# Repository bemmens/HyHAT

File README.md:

To Add: 
- PCB for Array
- PCB for Hypertronics
- Verasonics Code
- BOM
- Link to paper
- Structure of others to add their own designs 

Code to use a Verasonics Vantage System to control the array can be found at: https://github.com/bemmens/Verasonics-Acoustic-Tweezer

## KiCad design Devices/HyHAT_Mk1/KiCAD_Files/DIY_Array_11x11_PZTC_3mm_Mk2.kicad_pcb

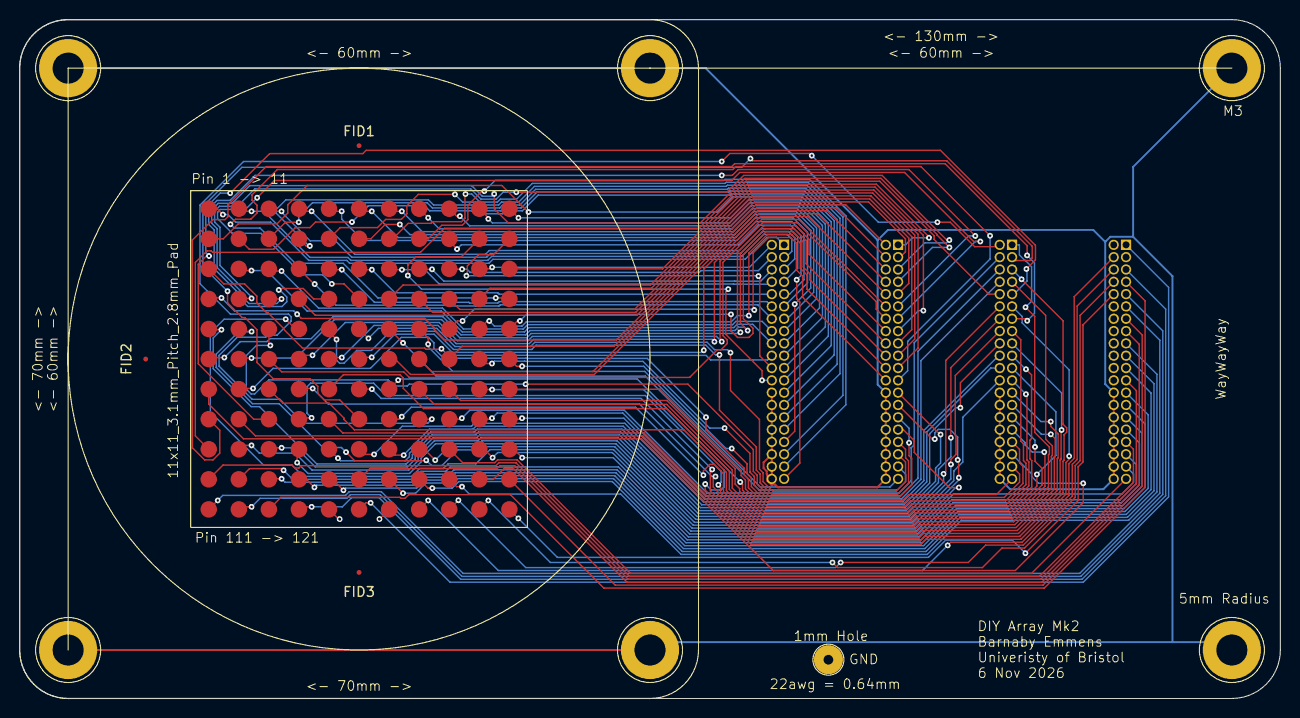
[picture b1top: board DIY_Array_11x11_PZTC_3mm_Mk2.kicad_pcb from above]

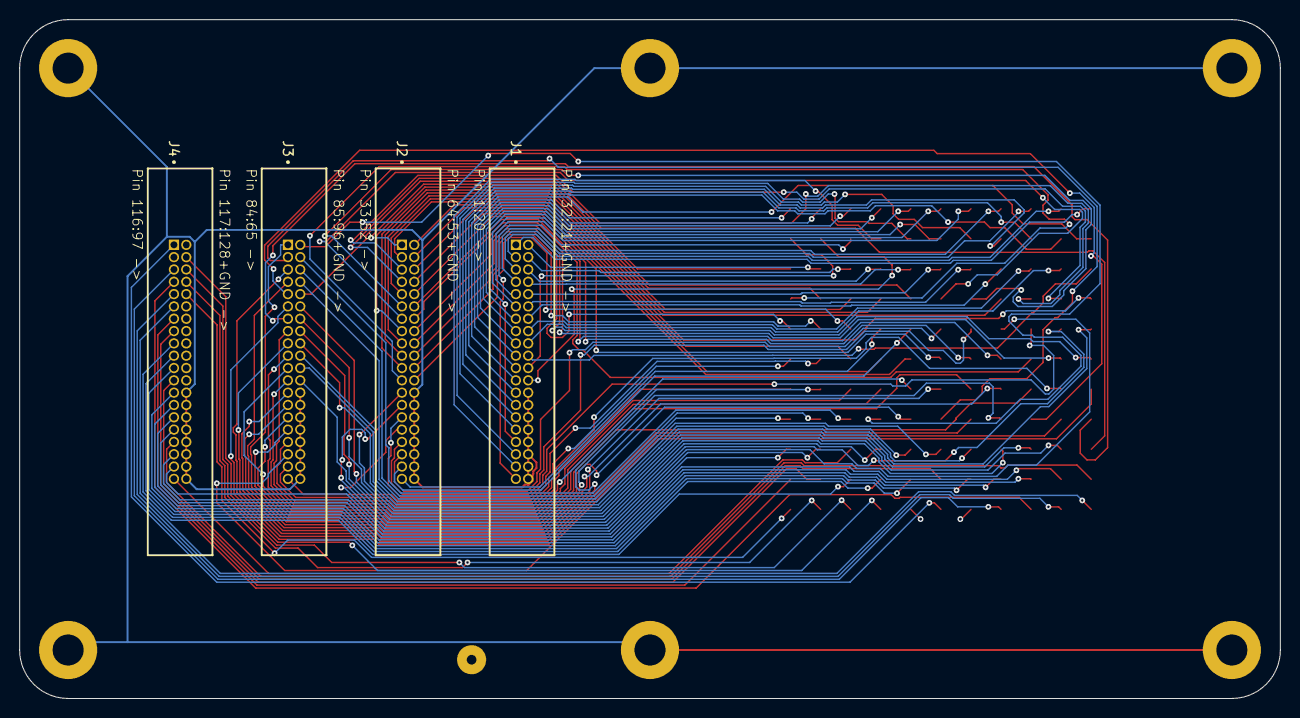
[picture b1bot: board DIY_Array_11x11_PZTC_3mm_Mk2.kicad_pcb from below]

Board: 4 copper layers, 130.0 x 70.0 mm, 15 parts (4 on the bottom side), 122 nets.

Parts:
AR1: PZTC_11x11_3mm_PogoPin
FID1, FID2, FID3: Fiducial_0.5mm_Mask1mm
GND**, GND**1, GND**2, GND**3, GND**4, GND**6: GND_M3
J1, J2, J3, J4: Samtech_2x20; SAMTEC_EHF-120-01-L-D
TP2: TestPoint; PTH_Single_Wire

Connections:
/GND: GND**.1, GND**1.1, GND**2.1, GND**3.1, GND**4.1, GND**6.1, J1.26, J1.28, J1.30, J1.32, J1.34, J1.36, J1.38, J1.40, J2.26, J2.28, J2.30, J2.32, J2.34, J2.36, J2.38, J2.40, J3.26, J3.28, J3.30, J3.32, J3.34, J3.36, J3.38, J3.40, J4.26, J4.28, J4.30, J4.32, J4.34, J4.36, J4.38, J4.40
/L1: AR1.1, J1.1
/L2: AR1.2, J1.3
/L3: AR1.3, J1.5
/L4: AR1.4, J1.7
/L5: AR1.5, J1.9
/L6: AR1.6, J1.11
/L7: AR1.7, J1.13
/L8: AR1.8, J1.15
/L9: AR1.9, J1.17
/L10: AR1.10, J1.19
/L11: AR1.11, J1.21
/L12: AR1.12, J1.23
/L13: AR1.13, J1.25
/L14: AR1.14, J1.27
/L15: AR1.15, J1.29
/L16: AR1.16, J1.31
/L17: AR1.17, J1.33
/L18: AR1.18, J1.35
/L19: AR1.19, J1.37
/L20: AR1.20, J1.39
/L21: AR1.21, J1.2
/L22: AR1.22, J1.4
/L23: AR1.23, J1.6
/L24: AR1.24, J1.8
/L25: AR1.25, J1.10
/L26: AR1.26, J1.12
/L27: AR1.27, J1.14
/L28: AR1.28, J1.16
/L29: AR1.29, J1.18
/L30: AR1.30, J1.20
/L31: AR1.31, J1.22
/L32: AR1.32, J1.24
/L33: AR1.33, J2.1
/L34: AR1.34, J2.3
/L35: AR1.35, J2.5
/L36: AR1.36, J2.7
/L37: AR1.37, J2.9
/L38: AR1.38, J2.11
/L39: AR1.39, J2.13
/L40: AR1.40, J2.15
/L41: AR1.41, J2.17
/L42: AR1.42, J2.19
/L43: AR1.43, J2.21
/L44: AR1.44, J2.23
/L45: AR1.45, J2.25
/L46: AR1.46, J2.27
/L47: AR1.47, J2.29
/L48: AR1.48, J2.31
/L49: AR1.49, J2.33
/L50: AR1.50, J2.35
/L51: AR1.51, J2.37
/L52: AR1.52, J2.39
/L53: AR1.53, J2.2
/L54: AR1.54, J2.4
/L55: AR1.55, J2.6
/L56: AR1.56, J2.8
/L57: AR1.57, J2.10
/L58: AR1.58, J2.12
/L59: AR1.59, J2.14
/L60: AR1.60, J2.16
/L61: AR1.61, J2.18
/L62: AR1.62, J2.20
/L63: AR1.63, J2.22
/L64: AR1.64, J2.24
/L65: AR1.65, J3.1
/L66: AR1.66, J3.3
/L67: AR1.67, J3.5
/L68: AR1.68, J3.7
/L69: AR1.69, J3.9
/L70: AR1.70, J3.11
/L71: AR1.71, J3.13
/L72: AR1.72, J3.15
/L73: AR1.73, J3.17
/L74: AR1.74, J3.19
/L75: AR1.75, J3.21
/L76: AR1.76, J3.23
/L77: AR1.77, J3.25
/L78: AR1.78, J3.27
/L79: AR1.79, J3.29
/L80: AR1.80, J3.31
/L81: AR1.81, J3.33
/L82: AR1.82, J3.35
/L83: AR1.83, J3.37
/L84: AR1.84, J3.39
/L85: AR1.85, J3.2
/L86: AR1.86, J3.4
/L87: AR1.87, J3.6
/L88: AR1.88, J3.8
/L89: AR1.89, J3.10
/L90: AR1.90, J3.12
/L91: AR1.91, J3.14
/L92: AR1.92, J3.16
/L93: AR1.93, J3.18
/L94: AR1.94, J3.20
/L95: AR1.95, J3.22
/L96: AR1.96, J3.24
/L97: AR1.97, J4.1
/L98: AR1.98, J4.3
/L99: AR1.99, J4.5
/L100: AR1.100, J4.7
/L101: AR1.101, J4.9
/L102: AR1.102, J4.11
/L103: AR1.103, J4.13
/L104: AR1.104, J4.15
/L105: AR1.105, J4.17
/L106: AR1.106, J4.19
/L107: AR1.107, J4.21
/L108: AR1.108, J4.23
/L109: AR1.109, J4.25
/L110: AR1.110, J4.27
/L111: AR1.111, J4.29
/L112: AR1.112, J4.31
/L113: AR1.113, J4.33
/L114: AR1.114, J4.35
/L115: AR1.115, J4.37
/L116: AR1.116, J4.39
/L117: AR1.117, J4.2
/L118: AR1.118, J4.4
/L119: AR1.119, J4.6
/L120: AR1.120, J4.8
/L121: AR1.121, J4.10

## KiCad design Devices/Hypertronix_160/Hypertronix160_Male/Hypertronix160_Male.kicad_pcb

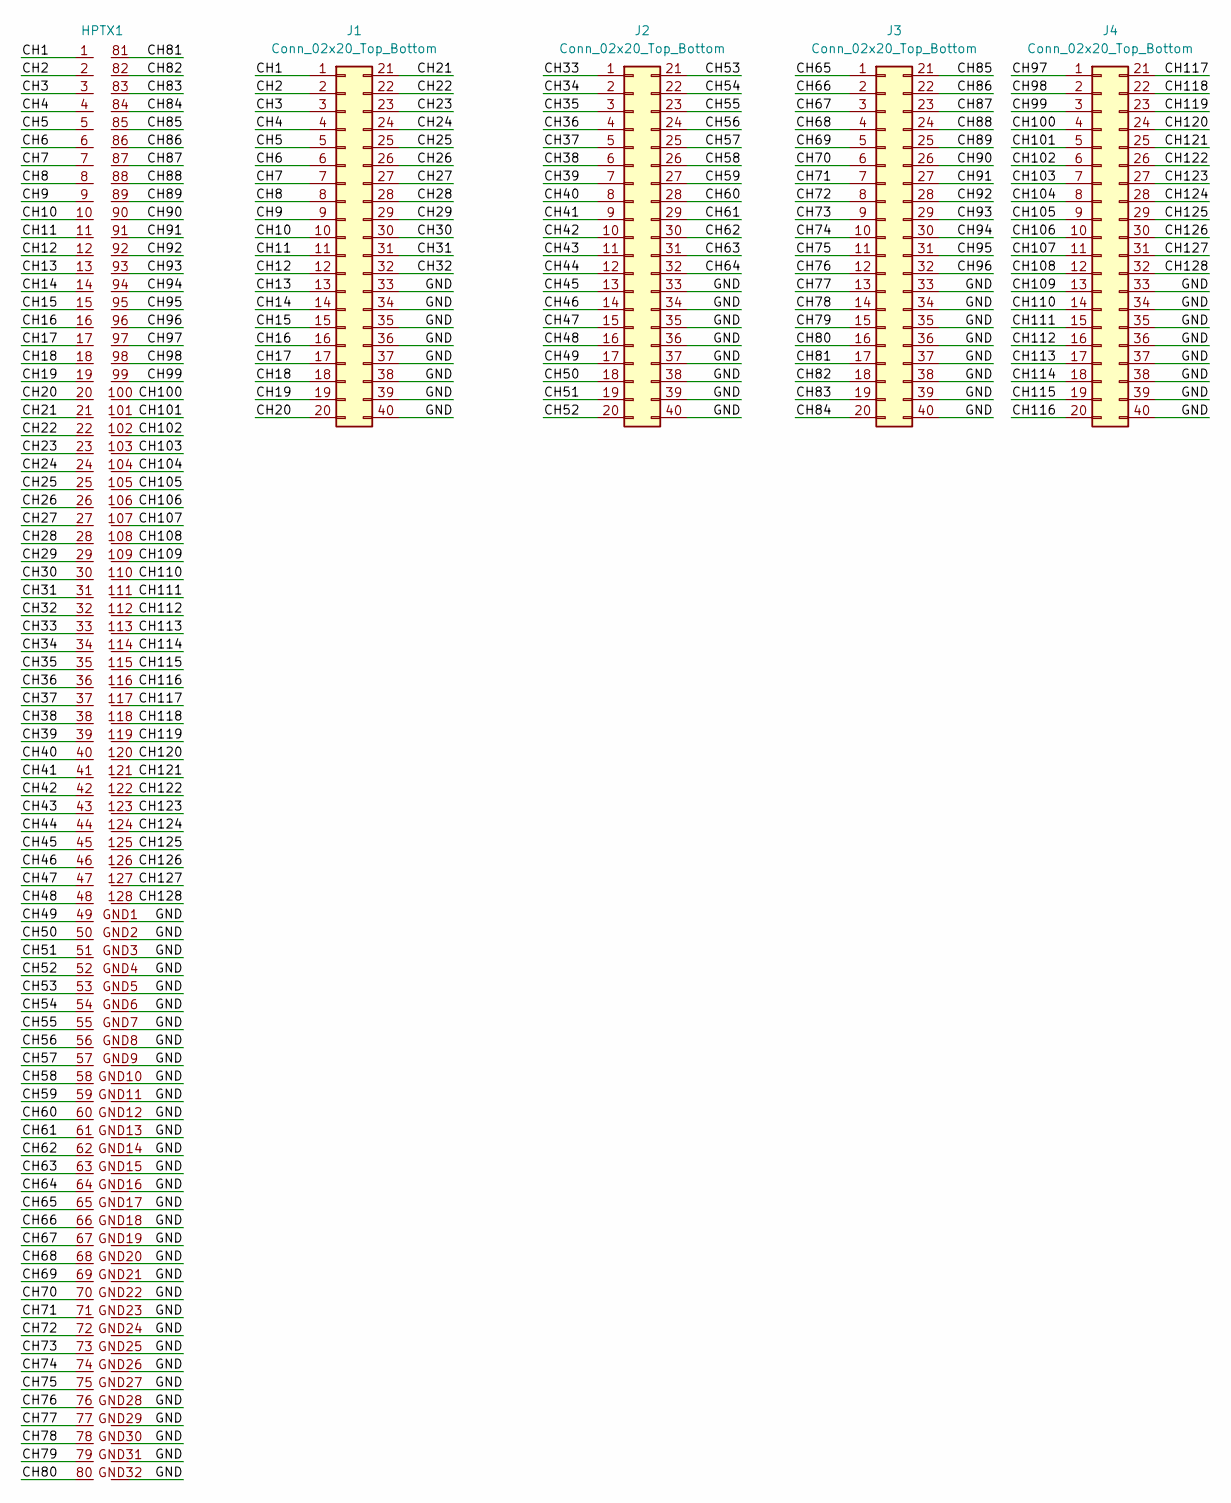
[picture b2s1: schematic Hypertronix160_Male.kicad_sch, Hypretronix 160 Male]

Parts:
HPTX1: Hypetronics_160_Mk2
J1, J2, J3, J4: Conn_02x20_Top_Bottom; SAMTEC_EHF-120-01-L-D

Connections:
/CH1: HPTX1.1 (L1), J1.1
/CH2: HPTX1.2 (L2), J1.2
/CH3: HPTX1.3 (L3), J1.3
/CH4: HPTX1.4 (L4), J1.4
/CH5: HPTX1.5 (L5), J1.5
/CH6: HPTX1.6 (L6), J1.6
/CH7: HPTX1.7 (L7), J1.7
/CH8: HPTX1.8 (L8), J1.8
/CH9: HPTX1.9 (L9), J1.9
/CH10: HPTX1.10 (L10), J1.10
/CH11: HPTX1.11 (L11), J1.11
/CH12: HPTX1.12 (L12), J1.12
/CH13: HPTX1.13 (L13), J1.13
/CH14: HPTX1.14 (L14), J1.14
/CH15: HPTX1.15 (L15), J1.15
/CH16: HPTX1.16 (L16), J1.16
/CH17: HPTX1.17 (L17), J1.17
/CH18: HPTX1.18 (L18), J1.18
/CH19: HPTX1.19 (L19), J1.19
/CH20: HPTX1.20 (L20), J1.20
/CH21: HPTX1.21 (L21), J1.21
/CH22: HPTX1.22 (L22), J1.22
/CH23: HPTX1.23 (L23), J1.23
/CH24: HPTX1.24 (L24), J1.24
/CH25: HPTX1.25 (L25), J1.25
/CH26: HPTX1.26 (L26), J1.26
/CH27: HPTX1.27 (L27), J1.27
/CH28: HPTX1.28 (L28), J1.28
/CH29: HPTX1.29 (L29), J1.29
/CH30: HPTX1.30 (L30), J1.30
/CH31: HPTX1.31 (L31), J1.31
/CH32: HPTX1.32 (L32), J1.32
/CH33: HPTX1.33 (L33), J2.1
/CH34: HPTX1.34 (L34), J2.2
/CH35: HPTX1.35 (L35), J2.3
/CH36: HPTX1.36 (L36), J2.4
/CH37: HPTX1.37 (L37), J2.5
/CH38: HPTX1.38 (L38), J2.6
/CH39: HPTX1.39 (L39), J2.7
/CH40: HPTX1.40 (L40), J2.8
/CH41: HPTX1.41 (L41), J2.9
/CH42: HPTX1.42 (L42), J2.10
/CH43: HPTX1.43 (L43), J2.11
/CH44: HPTX1.44 (L44), J2.12
/CH45: HPTX1.45 (L45), J2.13
/CH46: HPTX1.46 (L46), J2.14
/CH47: HPTX1.47 (L47), J2.15
/CH48: HPTX1.48 (L48), J2.16
/CH49: HPTX1.49 (L49), J2.17
/CH50: HPTX1.50 (L50), J2.18
/CH51: HPTX1.51 (L51), J2.19
/CH52: HPTX1.52 (L52), J2.20
/CH53: HPTX1.53 (L53), J2.21
/CH54: HPTX1.54 (L54), J2.22
/CH55: HPTX1.55 (L55), J2.23
/CH56: HPTX1.56 (L56), J2.24
/CH57: HPTX1.57 (L57), J2.25
/CH58: HPTX1.58 (L58), J2.26
/CH59: HPTX1.59 (L59), J2.27
/CH60: HPTX1.60 (L60), J2.28
/CH61: HPTX1.61 (L61), J2.29
/CH62: HPTX1.62 (L62), J2.30
/CH63: HPTX1.63 (L63), J2.31
/CH64: HPTX1.64 (L64), J2.32
/CH65: HPTX1.65 (L65), J3.1
/CH66: HPTX1.66 (L66), J3.2
/CH67: HPTX1.67 (L67), J3.3
/CH68: HPTX1.68 (L68), J3.4
/CH69: HPTX1.69 (L69), J3.5
/CH70: HPTX1.70 (L70), J3.6
/CH71: HPTX1.71 (L71), J3.7
/CH72: HPTX1.72 (L72), J3.8
/CH73: HPTX1.73 (L73), J3.9
/CH74: HPTX1.74 (L74), J3.10
/CH75: HPTX1.75 (L75), J3.11
/CH76: HPTX1.76 (L76), J3.12
/CH77: HPTX1.77 (L77), J3.13
/CH78: HPTX1.78 (L78), J3.14
/CH79: HPTX1.79 (L79), J3.15
/CH80: HPTX1.80 (L80), J3.16
/CH81: HPTX1.81, J3.17
/CH82: HPTX1.82, J3.18
/CH83: HPTX1.83, J3.19
/CH84: HPTX1.84, J3.20
/CH85: HPTX1.85, J3.21
/CH86: HPTX1.86, J3.22
/CH87: HPTX1.87, J3.23
/CH88: HPTX1.88, J3.24
/CH89: HPTX1.89, J3.25
/CH90: HPTX1.90, J3.26
/CH91: HPTX1.91, J3.27
/CH92: HPTX1.92, J3.28
/CH93: HPTX1.93, J3.29
/CH94: HPTX1.94, J3.30
/CH95: HPTX1.95, J3.31
/CH96: HPTX1.96, J3.32
/CH97: HPTX1.97, J4.1
/CH98: HPTX1.98, J4.2
/CH99: HPTX1.99, J4.3
/CH100: HPTX1.100, J4.4
/CH101: HPTX1.101, J4.5
/CH102: HPTX1.102, J4.6
/CH103: HPTX1.103, J4.7
/CH104: HPTX1.104, J4.8
/CH105: HPTX1.105, J4.9
/CH106: HPTX1.106, J4.10
/CH107: HPTX1.107, J4.11
/CH108: HPTX1.108, J4.12
/CH109: HPTX1.109, J4.13
/CH110: HPTX1.110, J4.14
/CH111: HPTX1.111, J4.15
/CH112: HPTX1.112, J4.16
/CH113: HPTX1.113, J4.17
/CH114: HPTX1.114, J4.18
/CH115: HPTX1.115, J4.19
/CH116: HPTX1.116, J4.20
/CH117: HPTX1.117, J4.21
/CH118: HPTX1.118, J4.22
/CH119: HPTX1.119, J4.23
/CH120: HPTX1.120, J4.24
/CH121: HPTX1.121, J4.25
/CH122: HPTX1.122, J4.26
/CH123: HPTX1.123, J4.27
/CH124: HPTX1.124, J4.28
/CH125: HPTX1.125, J4.29
/CH126: HPTX1.126, J4.30
/CH127: HPTX1.127, J4.31
/CH128: HPTX1.128, J4.32
/GND: HPTX1.GND1, HPTX1.GND2, HPTX1.GND3, HPTX1.GND4, HPTX1.GND5, HPTX1.GND6, HPTX1.GND7, HPTX1.GND8, HPTX1.GND9, HPTX1.GND10, HPTX1.GND11, HPTX1.GND12, HPTX1.GND13, HPTX1.GND14, HPTX1.GND15, HPTX1.GND16, HPTX1.GND17, HPTX1.GND18, HPTX1.GND19, HPTX1.GND20, HPTX1.GND21, HPTX1.GND22, HPTX1.GND23, HPTX1.GND24, HPTX1.GND25, HPTX1.GND26, HPTX1.GND27, HPTX1.GND28, HPTX1.GND29, HPTX1.GND30, HPTX1.GND31, HPTX1.GND32, J1.33, J1.34, J1.35, J1.36, J1.37, J1.38, J1.39, J1.40, J2.33, J2.34, J2.35, J2.36, J2.37, J2.38, J2.39, J2.40, J3.33, J3.34, J3.35, J3.36, J3.37, J3.38, J3.39, J3.40, J4.33, J4.34, J4.35, J4.36, J4.37, J4.38, J4.39, J4.40

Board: 4 copper layers, 9 parts (4 on the bottom side), 129 nets, no tracks yet.

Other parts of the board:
Mount1, Mount2, Mount3, Mount4: MountingHole_3.2mm_M3_DIN965_Pad
